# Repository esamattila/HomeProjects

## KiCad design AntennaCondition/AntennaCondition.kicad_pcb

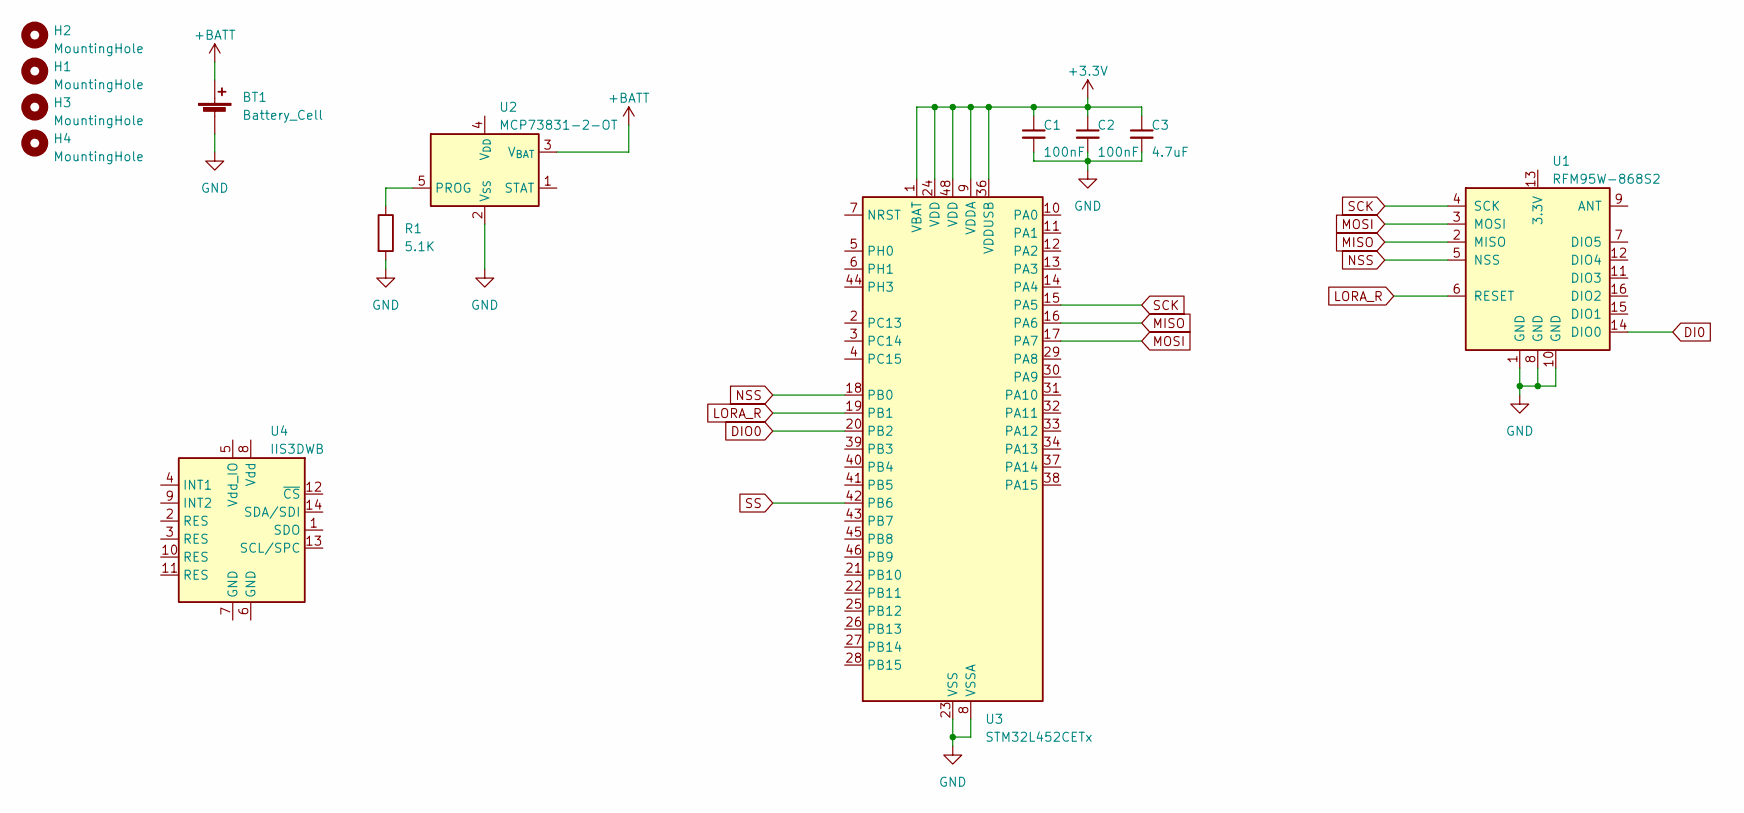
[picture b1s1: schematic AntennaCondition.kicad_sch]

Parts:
BT1: Battery_Cell; BatteryHolder_MPD_BH-18650-PC2
C1, C2: 100nF; C_0603_1608Metric
C3: 4.7uF; C_0603_1608Metric
H1, H2, H3, H4: MountingHole; MountingHole_3.2mm_M3
R1: 5.1K; C_0603_1608Metric
U1: RFM95W-868S2; HOPERF_RFM9XW_SMD
U2: MCP73831-2-OT; SOT-23-5
U3: STM32L452CETx; LQFP-48_7x7mm_P0.5mm
U4: IIS3DWB; LGA-14_3x2.5mm_P0.5mm_LayoutBorder3x4y

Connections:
+3.3V: C1.1, C2.1, C3.1, U3.1 (VBAT), U3.9 (VDDA), U3.24 (VDD), U3.36 (VDDUSB), U3.48 (VDD)
+BATT: BT1.1 (+), U2.3 (V_{BAT})
DI0: U1.14 (DIO0)
DIO0: U3.20 (PB2)
GND: BT1.2 (-), C1.2, C2.2, C3.2, R1.2, U1.1 (GND), U1.8 (GND), U1.10 (GND), U2.2 (V_{SS}), U3.8 (VSSA), U3.23 (VSS), U3.35 (VSS), U3.47 (VSS)
LORA_R: U1.6 (RESET), U3.19 (PB1)
MISO: U1.2 (MISO), U3.16 (PA6)
MOSI: U1.3 (MOSI), U3.17 (PA7)
NSS: U1.5 (NSS), U3.18 (PB0)
unnamed: R1.1, U2.5 (PROG)
SCK: U1.4 (SCK), U3.15 (PA5)
SS: U3.42 (PB6)

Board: 2 copper layers, 12 parts (0 on the bottom side), 9 nets, no tracks yet.
